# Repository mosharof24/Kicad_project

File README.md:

This is a simple pcb design of a usb to serial converter based on ch340 chip.This project is done in KiCad 6(Linux).

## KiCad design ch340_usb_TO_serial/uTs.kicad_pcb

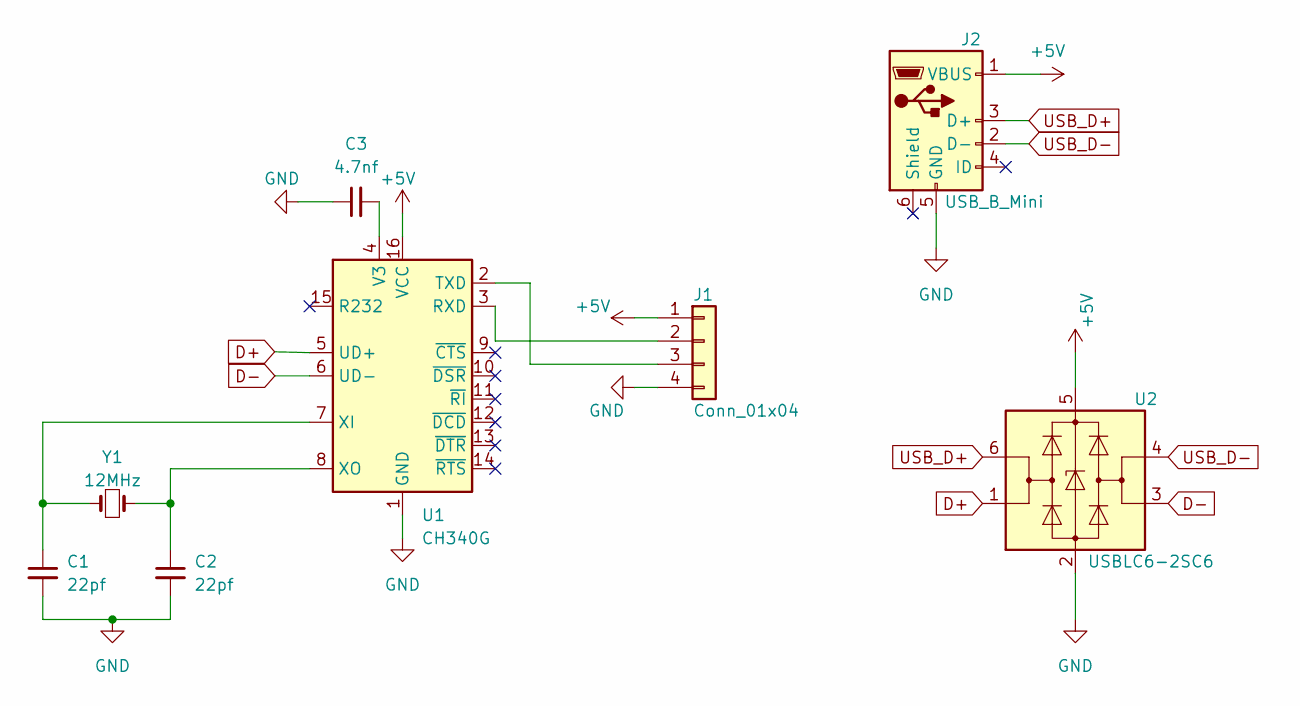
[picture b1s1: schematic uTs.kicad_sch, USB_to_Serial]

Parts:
C1, C2: 22pf; C_0603_1608Metric
C3: 4.7nf; C_0603_1608Metric
J1: Conn_01x04; PinHeader_1x04_P1.00mm_Vertical
J2: USB_B_Mini; USB_Mini-B_Wuerth_65100516121_Horizontal
U1: CH340G; SOIC-16_3.9x9.9mm_P1.27mm
U2: USBLC6-2SC6; SOT-23-6
Y1: 12MHz; Crystal_SMD_0603-2Pin_6.0x3.5mm

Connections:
+5V: J1.1, J2.1 (VBUS), U1.16 (VCC), U2.5 (VBUS)
D+: U1.5 (UD+), U2.1 (I/O1)
D-: U1.6 (UD-), U2.3 (I/O2)
GND: C1.2, C2.2, C3.1, J1.4, J2.5 (GND), U1.1 (GND), U2.2 (GND)
unnamed: C1.1, U1.7 (XI), Y1.1
unnamed: C2.1, U1.8 (XO), Y1.2
unnamed: C3.2, U1.4 (V3)
unnamed: J1.2, U1.3 (RXD)
unnamed: J1.3, U1.2 (TXD)
USB_D+: J2.3 (D+), U2.6 (I/O1)
USB_D-: J2.2 (D-), U2.4 (I/O2)

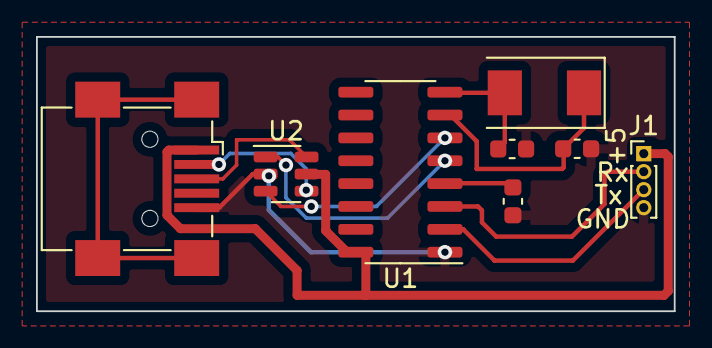
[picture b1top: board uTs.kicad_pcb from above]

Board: 2 copper layers, 35.4 x 15.2 mm, 8 parts (0 on the bottom side), 11 nets.
